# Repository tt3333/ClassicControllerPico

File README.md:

[日本語版 README はこちら](README-ja.md)

# Classic Controller Pico

Classic Controller Pico is a program that allows Raspberry Pi Pico to be recognized as Wii classic controller.

This project is based off of the [Wii RetroPad Adapter](https://github.com/bootsector/wii-retropad-adapter) project by Bruno Freitas.<BR>
The license for this project follows the license for the Wii RetroPad adapter.

## Tested Hardware

* WiiU (via Wii Remote)
* SNES Classic Edition
* ELECOM JC-W01UWH
* Columbus Circle CC-NSSCV-RD
* [Controller Converter for Switch](https://github.com/tt3333/ControllerConverterForSwitch)

## How to Build Hardware

### Ordering PCBs

#### If you place an order with JLCPCB and want the order number printed in an inconspicuous location

Upload gerber_JLCPCB.zip and select "Specify a location" from the "Remove Order Number" options.

#### If you place an order with JLCPCB and do not want the order number printed

Upload gerber.zip and select "Yes" from the "Remove Order Number" options.<BR>
However, if Yes is selected, an optional fee will be charged.

#### For orders outside of JLCPCB

Upload gerber.zip.

### Assembly

* Solder 2kΩ resistors to R1 and R2.<BR>
  (Built-in pull-up resistors in Raspberry Pi Pico are too high in resistance, so communication is not stable without external pull-up resistors.)
* Solder a Schottky barrier diode (1N5819) to D1.
* Solder sockets to U1 and mount a Raspberry Pi Pico.
* Cut the extension cable for Wii in half and connect the Male cable to CN1.
* Connect buttons of your choice to each terminals of CN2.
* At this time, CN3 does not need to be connected to anything.<BR>
  (A future version may support analog stick connection.)
* CN4 is for debugging firmware, so normally nothing needs to be connected.
* While pressing the BOOTSEL button on the Raspberry Pi Pico, connect the USB cable and write the firmware.ino.uf2.

### Example of Use

This is an example of two MS-350Ms from Marushin electric mfg. installed on a SW-130 from TAKACHI ELECTRONICS ENCLOSURE.<BR>
Pin headers are used so that button assignments can be easily changed by simply replacing the connectors.<BR>
Note the following points because the case is just barely high enough when the connectors is inserted into the pin headers.

* When ordering PCBs from JLCPCB, I chose 0.8mm for "PCB Thickness" instead of the standard 1.6mm.
  (I made it as thin as possible without incurring any additional charges.)
* By using a nuts instead of spacers and securing the board between the nut and nut, the gap between the board and case is reduced to one nut.
* To reduce the protrusion of the backside of the board, not only resistors and diodes but also the pins of IC sockets and pin headers are cut short.
* Rubber cushions are attached to the back surface to prevent slipping when operating with the feet.

## If you modify firmware

If you connect a USB serial converter to CN4 and enable `#define DEBUG` in config.h, debug output is available.

### How to Build Firmware

1. Install Arduino IDE
2. Open firmware.ino
3. Click "File", then "Preferences..."
4. Copy and paste the following URL into the "Additional boards manager URLs" field and click "OK"<BR>
   `https://github.com/earlephilhower/arduino-pico/releases/download/global/package_rp2040_index.json`
5. Click "Tools", "Board", then "Board Manager..."
6. Type "pico" in the search field and install "Raspberry Pi Pico/RP2040 by Earle F. Philhower, III"
7. Click "Tools", "Board", "Raspberry Pi Pico/RP2040", then "Raspberry Pi Pico"
8. Click "Tools", "Optimize", then "Fast (-Ofast) (maybe slower)"
9. Click "Sketch", then "Export Compiled Binary"

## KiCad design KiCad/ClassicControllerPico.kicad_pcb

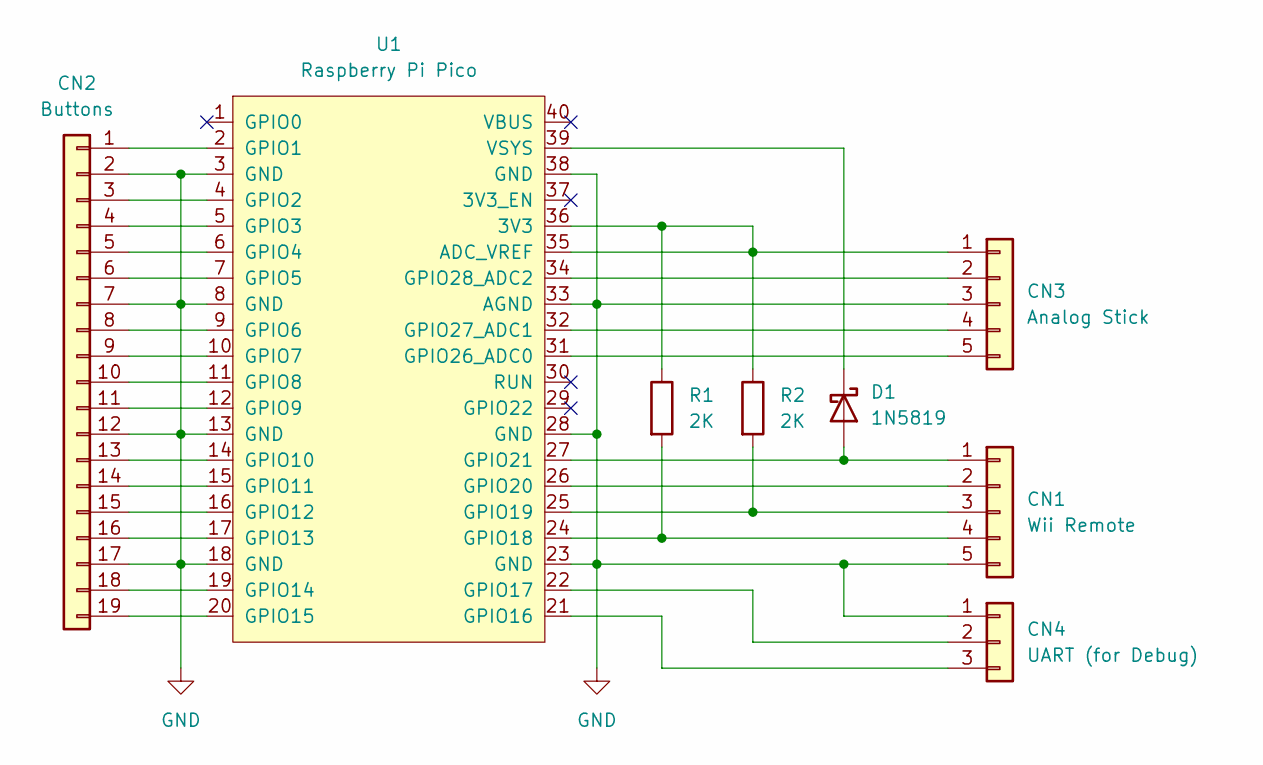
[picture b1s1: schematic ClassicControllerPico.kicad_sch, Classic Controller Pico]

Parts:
CN1: Wii Remote; PinHeader_1x05_P2.54mm_Vertical
CN2: Buttons; PinHeader_1x19_P2.54mm_Vertical
CN3: Analog Stick; PinHeader_1x05_P2.54mm_Vertical
CN4: UART (for Debug); PinHeader_1x03_P2.54mm_Vertical
D1: 1N5819; D_DO-41_SOD81_P10.16mm_Horizontal
R1, R2: 2K; R_Axial_DIN0207_L6.3mm_D2.5mm_P10.16mm_Horizontal
U1: Raspberry Pi Pico; RPi_Pico_SMD_TH

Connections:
GND: CN1.5, CN2.2, CN2.7, CN2.12, CN2.17, CN3.3, CN4.1, U1.3 (GND), U1.8 (GND), U1.13 (GND), U1.18 (GND), U1.23 (GND), U1.28 (GND), U1.33 (AGND), U1.38 (GND)
unnamed: CN1.1, D1.2 (A), U1.27 (GPIO21)
unnamed: CN1.2, U1.26 (GPIO20)
unnamed: CN1.3, R2.2, U1.25 (GPIO19)
unnamed: CN1.4, R1.2, U1.24 (GPIO18)
unnamed: CN2.1, U1.2 (GPIO1)
unnamed: CN2.3, U1.4 (GPIO2)
unnamed: CN2.4, U1.5 (GPIO3)
unnamed: CN2.5, U1.6 (GPIO4)
unnamed: CN2.6, U1.7 (GPIO5)
unnamed: CN2.8, U1.9 (GPIO6)
unnamed: CN2.9, U1.10 (GPIO7)
unnamed: CN2.10, U1.11 (GPIO8)
unnamed: CN2.11, U1.12 (GPIO9)
unnamed: CN2.13, U1.14 (GPIO10)
unnamed: CN2.14, U1.15 (GPIO11)
unnamed: CN2.15, U1.16 (GPIO12)
unnamed: CN2.16, U1.17 (GPIO13)
unnamed: CN2.18, U1.19 (GPIO14)
unnamed: CN2.19, U1.20 (GPIO15)
unnamed: CN3.1, R1.1, R2.1, U1.35 (ADC_VREF), U1.36 (3V3)
unnamed: CN3.2, U1.34 (GPIO28_ADC2)
unnamed: CN3.4, U1.32 (GPIO27_ADC1)
unnamed: CN3.5, U1.31 (GPIO26_ADC0)
unnamed: CN4.2, U1.22 (GPIO17)
unnamed: CN4.3, U1.21 (GPIO16)
unnamed: D1.1 (K), U1.39 (VSYS)

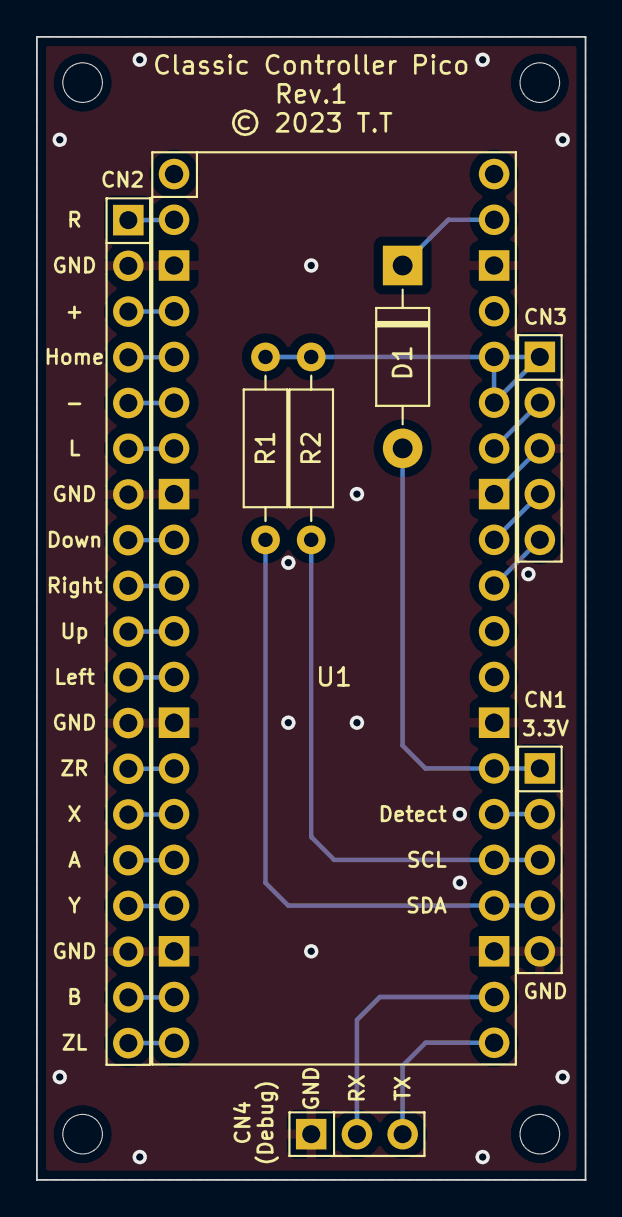
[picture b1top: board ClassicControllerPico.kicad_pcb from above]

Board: 2 copper layers, 30.5 x 63.5 mm, 8 parts (0 on the bottom side), 27 nets.

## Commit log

2023-08-13 add .gitignore
2023-08-18 add firmware project
    This commit is experimental implementation.
    It works on SNES Classic, but probably will not work on Wii or WiiU because the cipher is not yet implemented.
2023-08-18 update copyright
2023-08-18 add WMExtension and WMCrypt
    https://github.com/bootsector/wii-retropad-adapter
    ede0f75eafa385dd38f72d6af3e78012f069f64b
2023-08-18 change to new Arduino API
2023-08-18 add wire to WMExtension::init argument
2023-08-18 change charactor encoding and newline code
2023-08-18 add format 2 support
2023-08-18 change WMExtension::set_button_data argument
2023-08-18 use WMExtension and WMCrypt
2023-08-18 add test code
2023-08-29 add schematic
2023-08-29 add KiCad project
2023-08-29 add firmware binary
2023-08-29 add gerber file
2023-08-29 add README
2024-02-10 Fixed a bug that the first read after a data format change sends data in the format before the change.
2024-03-24 Corrected a typo in the README

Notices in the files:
KiCad/ClassicControllerPico.kicad_pcb:
© 2023 T.T
